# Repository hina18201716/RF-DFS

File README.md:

# Radio Frequency Direction Finding System

The RF-DFS is a controllable 3-meter dish antenna with azimuth and elevation drivers to locate the source of RF interference. Located in this repo is information to connect the motor controllers and a PCB with an upgraded amplifier chain using Mini-Circuits PMA2-63LN+ SMT LNAs.

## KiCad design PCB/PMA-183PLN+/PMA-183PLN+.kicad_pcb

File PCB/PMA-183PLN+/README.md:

# Changelog

## Revision B - 7/5/2023

### Added

- More PTH vias around and directly under RF components.
- Another layer of via picketing around transmission line.
- Silkscreen revision indicator.

### Changed

- Removed Hammond 1554B compatibility due to difficulties in assembly and weatherproofing SMA connectors.

### Fixed

- C9 footprint now correctly matches schematic (0402 --> 1206).
- Moved SMA footprints closer to board edge to reduce filing prior to assembly.

## Revision A - 6/12/2023

### First revision 🎉🎉🎉

- Board is built to 4-layer OSHPark specifications
- Testing shows amplifier oscillates strongly at ~18.5 GHz. This occurs both when the amplifier is biased through the regulator or directly from a DC power supply. SMA landings were also copied from test coupons so that can likely be ruled out. This is possibly due to the lack of PTH vias directly under the IC or the tuning/spacing of picketing around the transmission line.

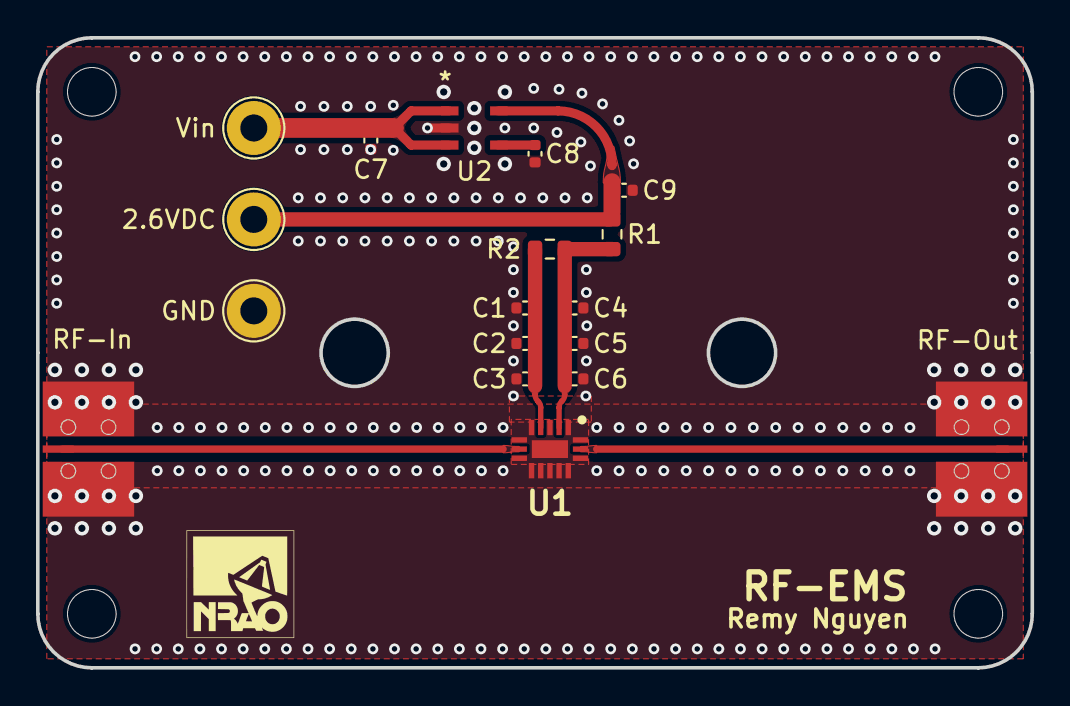
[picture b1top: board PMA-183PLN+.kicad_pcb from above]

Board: 4 copper layers, 55.3 x 35.0 mm, 20 parts (0 on the bottom side), 8 nets.

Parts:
2.6VDC: 2.6VDC; TestPoint_Loop_D2.54mm_Drill1.5mm_Beaded
 : FabDrawing-4Layer-Metric-Compact-OSH
 #2: LOGO; GCPW_osh2_90mm_user
C1, C4, C7: 0.33 uF; C_0402_1005Metric
C2, C5: 1000 pF; C_0402_1005Metric
C3, C6: 100 pF; C_0402_1005Metric
C8: 470 pF; C_0402_1005Metric
C9: 2.2 uF; C_0402_1005Metric
GND: GND; TestPoint_Loop_D2.54mm_Drill1.5mm_Beaded
R1: 10 Ω; R_0603_1608Metric
R2: 180 Ω; R_0603_1608Metric
RF-In: Conn_Coaxial; Mueller BU-1420761881
RF-Out: Conn_Coaxial; Mueller BU-1420761881
U1: PMA-183PLN+; QFN51P250X350X85-17N
U2: MIC5219-2.6YM5-TR; SOT-23-5_M5_MCH
Vin: Vin; TestPoint_Loop_D2.54mm_Drill1.5mm_Beaded

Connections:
2.6VDC: 2.6VDC.1, C9.1, R1.2, U2.5 (OUT)
GND: C1.1, C2.1, C3.1, C4.2, C5.2, C6.2, C7.2, C8.2, C9.2, GND.1, RF-In.2 (Ext), RF-Out.2 (Ext), U1.1 (NC_1), U1.3 (NC_2), U1.5 (NC_3), U1.6 (GND_1), U1.8 (GND_2), U1.9 (NC_4), U1.10 (NC_5), U1.11 (NC_6), U1.12 (NC_7), U1.13 (NC_8), U1.14 (GND_3), U1.16 (GND_4), U1.17 (EP), U2.2 (GND)
unnamed: RF-In.1 (In), U1.7 (RF-IN)
unnamed: RF-Out.1 (In), U1.15 (RF-OUT)
unnamed: C4.1, C5.1, C6.1, R1.1, R2.2, U1.2 (VDD)
unnamed: C1.2, C2.2, C3.2, R2.1, U1.4 (VE)
unnamed: C8.1, U2.4 (BYP)
Vin: C7.1, U2.1 (IN), U2.3 (EN), Vin.1

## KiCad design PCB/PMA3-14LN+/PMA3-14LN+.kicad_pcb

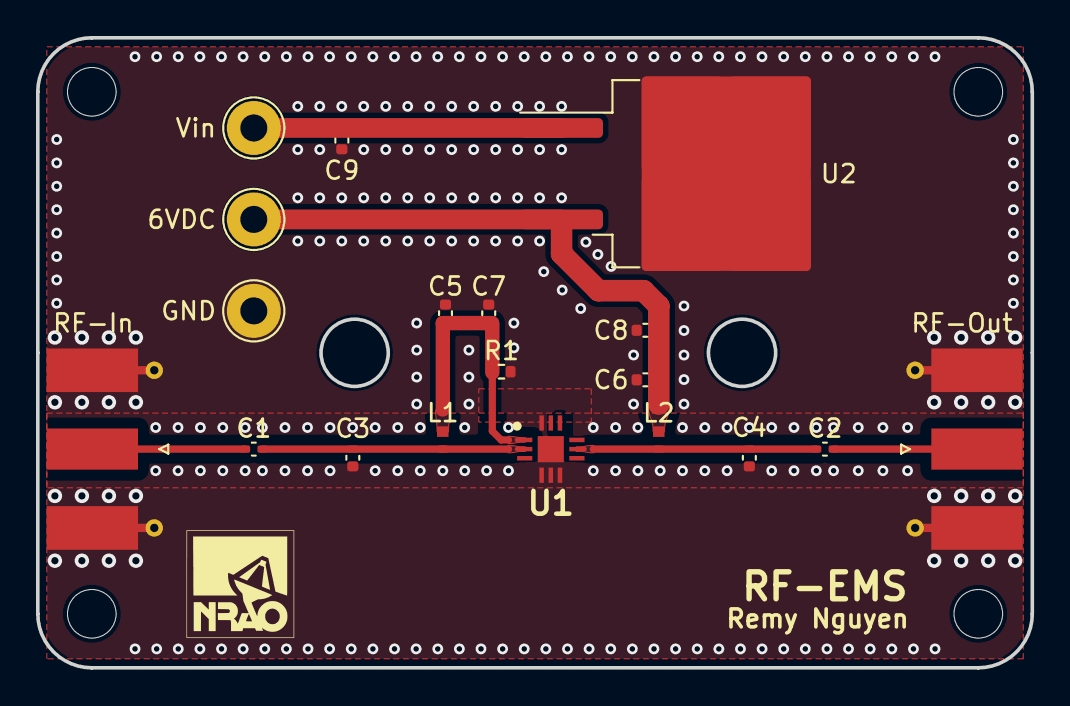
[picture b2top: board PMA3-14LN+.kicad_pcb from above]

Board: 4 copper layers, 55.3 x 35.0 mm, 20 parts (0 on the bottom side), 8 nets.

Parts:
6VDC: 6VDC; TestPoint_Loop_D2.54mm_Drill1.5mm_Beaded
 : FabDrawing-4Layer-Metric-Compact-OSH
C1, C2: 0.01 uF; C_0402_1005Metric
C3: 0.2 pF; C_0402_1005Metric
C4: 0.1 pF; C_0402_1005Metric
C5, C6: 100 pF; C_0402_1005Metric
C7: 0.1 uF; C_0402_1005Metric
C8: 0.1 uf; C_0402_1005Metric
C9: 0.33 uF; C_0402_1005Metric
GND: GND; TestPoint_Loop_D2.54mm_Drill1.5mm_Beaded
L1, L2: 900 nH; L_0402_1005Metric
R1: 510 Ω; R_0402_1005Metric
RF-In: Conn_Coaxial; SMA_Molex_73251-1153_EdgeMount_Horizontal_TunedOSH
RF-Out: Conn_Coaxial; SMA_Molex_73251-1153_EdgeMount_Horizontal_TunedOSH
U1: PMA3-14LN+; QFN51P300X300X89-13N
U2: L7806; TO-263-2
Vin: Vin; TestPoint_Loop_D2.54mm_Drill1.5mm_Beaded

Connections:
6VDC: 6VDC.1, C6.1, C8.1, L2.1, U2.3 (OUT)
GND: C3.1, C4.1, C5.1, C6.2, C7.1, C8.2, C9.2, GND.1, R1.2, RF-In.2 (Ext), RF-Out.2 (Ext), U1.3 (NC_1), U1.4 (NC_2), U1.5 (NC_3), U1.6 (NC_4), U1.7 (NC_5), U1.9 (NC_6), U1.11 (NC_8), U1.12 (NC_9), U1.13 (GND), U2.2 (GND)
unnamed: C5.2, C7.2, L1.1, R1.1, U1.1 (CURRENT_MIRROR)
unnamed: C1.2, C3.2, L1.2, U1.2 (RF-IN)
unnamed: C2.1, C4.2, L2.2, U1.8 (RF-OUT_&_VDD)
unnamed: C1.1, RF-In.1 (In)
unnamed: C2.2, RF-Out.1 (In)
Vin: C9.1, U2.1 (IN), Vin.1

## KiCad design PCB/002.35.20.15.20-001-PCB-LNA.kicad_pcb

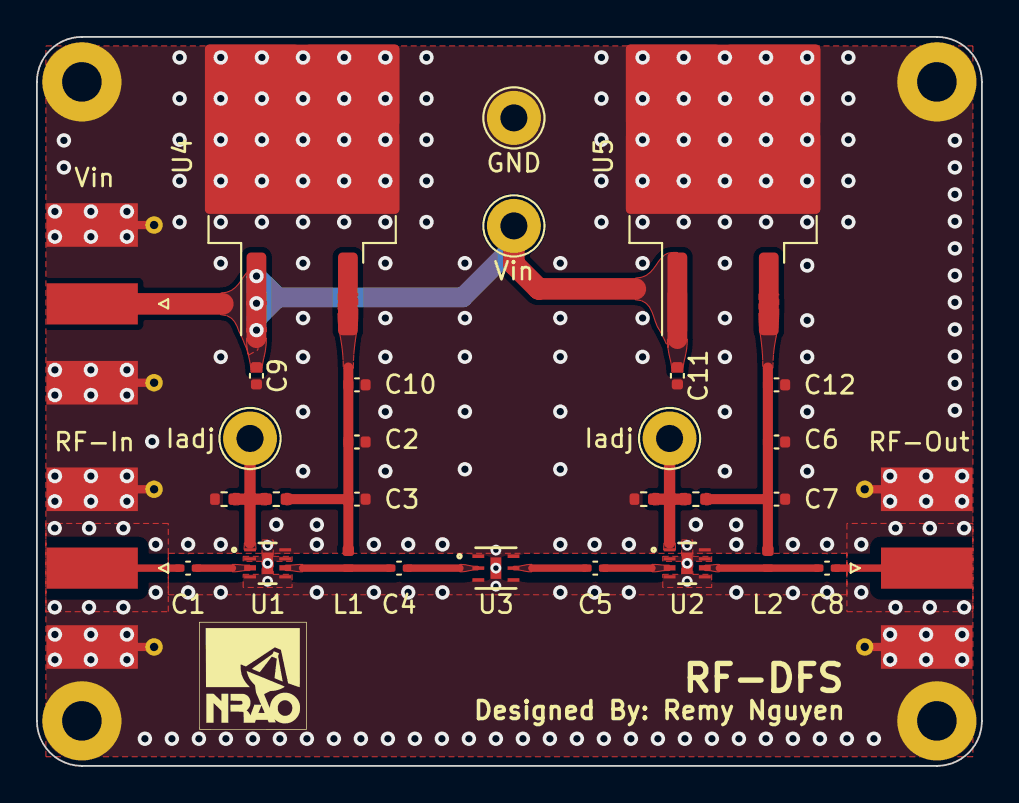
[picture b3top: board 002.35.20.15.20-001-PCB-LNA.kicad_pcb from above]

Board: 4 copper layers, 52.5 x 40.5 mm, 30 parts (0 on the bottom side), 14 nets.

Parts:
C1, C4, C5, C8: 150pF; C_0402_1005Metric
C2, C6: 1uF; C_0402_1005Metric
C3, C7: 100pF; C_0402_1005Metric
C9, C11: 0.33uF; C_0402_1005Metric
C10, C12: 0.1uF; C_0402_1005Metric
GND: GND; TestPoint_Loop_D2.54mm_Drill1.5mm_Beaded
Iadj: TestPoint; TestPoint_Loop_D2.54mm_Drill1.5mm_Beaded
Iadj#2: TestPoint; TestPoint_Loop_D2.54mm_Drill1.5mm_Beaded
L1, L2: 56nH; L_0402_1005Metric
R1, R2, R3, R4: 100k; R_0402_1005Metric
RF-In: Conn_Coaxial; SMA_Molex_73251-1153_EdgeMount_Horizontal
RF-Out: Conn_Coaxial; SMA_Molex_73251-1153_EdgeMount_Horizontal
U1, U2: PMA2-63LN+; SON8_PMA2_MNC
U3: YAT-1A+; MC1630_MNC
U4, U5: L7805; TO-263-2
Vin: Vin; TestPoint_Loop_D2.54mm_Drill1.5mm_Beaded
Vin#2: Conn_Coaxial; SMA_Molex_73251-1153_EdgeMount_Horizontal

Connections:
/LNA Biasing1/LNA-IN: C1.1, RF-In.1 (In)
/LNA Biasing1/LNA-OUT: C4.2, U3.2 (RF-IN)
/LNA Biasing2/LNA-IN: C5.1, U3.5 (RF-OUT)
/LNA Biasing2/LNA-OUT: C8.2, RF-Out.1 (In)
GND: C2.2, C3.2, C6.2, C7.2, C9.2, C10.2, C11.2, C12.2, GND.1, R1.1, R2.1, RF-In.2 (Ext), RF-Out.2 (Ext), U1.2 (GND), U1.4 (GND), U1.5 (GND), U1.7 (GND), U1.8 (GND), U1.9 (EPAD), U2.2 (GND), U2.4 (GND), U2.5 (GND), U2.7 (GND), U2.8 (GND), U2.9 (EPAD), U3.1 (GND), U3.3 (GND), U3.4 (GND), U3.6 (GND), U3.7 (GND), U4.2 (GND), U5.2 (GND), Vin#2.2 (Ext)
unnamed: Iadj#2.1, R1.2, R3.1, U1.1 (LADJ)
unnamed: C1.2, U1.3 (RF-IN)
unnamed: C4.1, L1.2, U1.6 (RF-OUT)
unnamed: Iadj.1, R2.2, R4.1, U2.1 (LADJ)
unnamed: C5.2, U2.3 (RF-IN)
unnamed: C8.1, L2.2, U2.6 (RF-OUT)
Vdd1: C2.1, C3.1, C10.1, L1.1, R3.2, U4.3 (OUT)
Vdd2: C6.1, C7.1, C12.1, L2.1, R4.2, U5.3 (OUT)
Vin: C9.1, C11.1, U4.1 (IN), U5.1 (IN), Vin.1, Vin#2.1 (In)

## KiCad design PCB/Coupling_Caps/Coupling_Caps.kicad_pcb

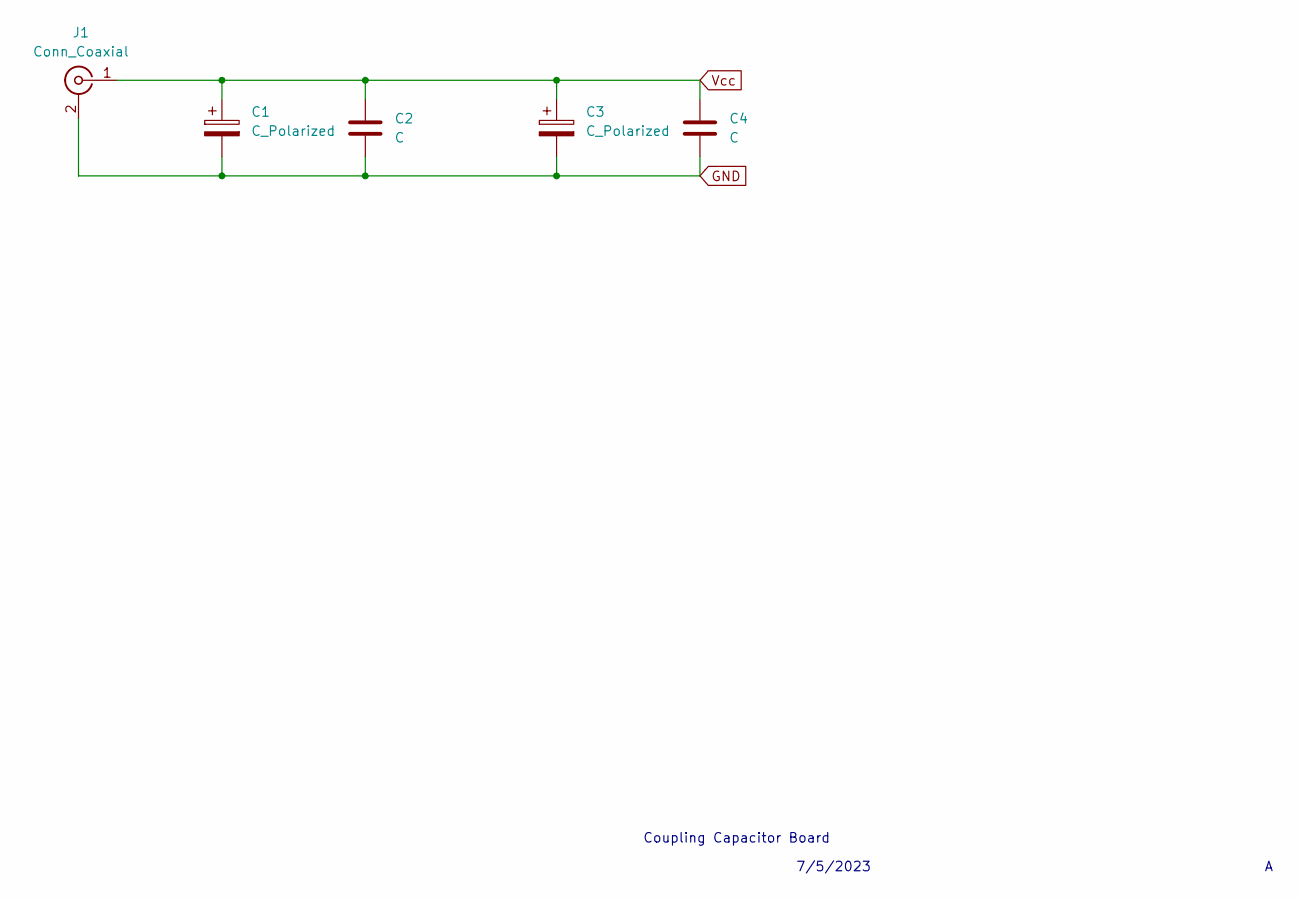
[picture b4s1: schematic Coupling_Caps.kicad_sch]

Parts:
C1, C3: C_Polarized; C_1206_3216Metric
C2, C4: C; C_1206_3216Metric
J1: Conn_Coaxial; SMA_Molex_73251-1153_EdgeMount_Horizontal

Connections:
GND: C1.2, C2.2, C3.2, C4.2, J1.2 (Ext)
Vcc: C1.1, C2.1, C3.1, C4.1, J1.1 (In)

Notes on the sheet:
Coupling Capacitor Board
7/5/2023

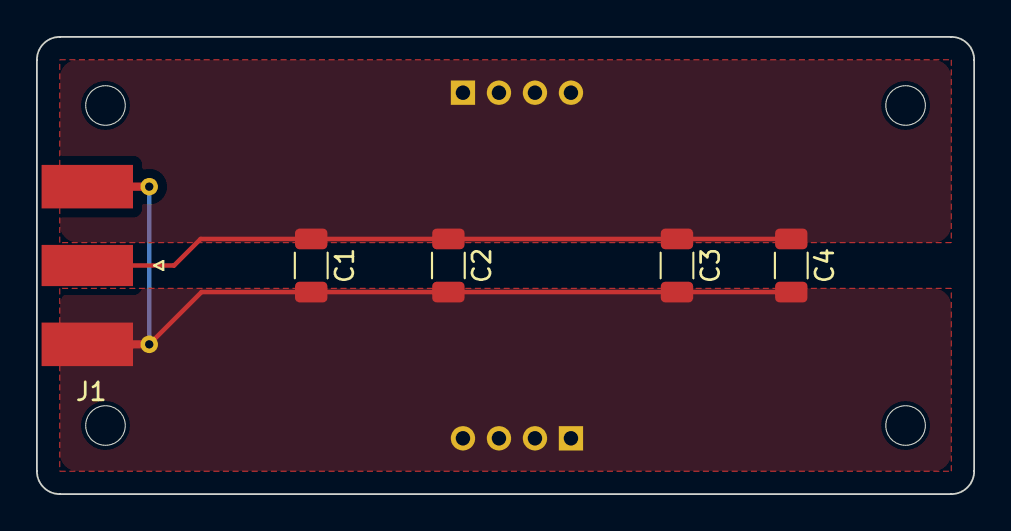
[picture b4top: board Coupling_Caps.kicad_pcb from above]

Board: 2 copper layers, 52.1 x 25.4 mm, 5 parts (0 on the bottom side), 2 nets.

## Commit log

2023-07-06 Initial local commit
2023-07-06 Footprints assigned, ERC pass
2023-07-06 PCB Rev A Complete, DRC Pass
2023-07-07 PTH vias and mounting holes added
2023-07-07 Bill of materials added
2023-07-10 Relocated PTH vias, removed backups
2023-07-10 --no-edit
2023-07-10 10 mil RO4350B --> 30 mil, RF traces adjusted
2023-07-11 Added .gitignore
2023-07-21 Added wiring diagram
2023-07-24 Wiring diagram completed
2023-07-26 Added document numbers
2023-08-02 Added PMA2-63LN+ s-parameters
2023-08-15 6 GHz s-params graphed
2023-08-16 Housekeeping
2023-08-21 Added board comments and assembly plot
2024-01-22 Fixed SMA pad thickness
2024-01-23 PCB Rev B complete: compacted board and fixed sma pads
2024-01-26 Updated board for Oshpark specifications
2024-01-31 New matlab directory with stability simulation
2024-01-31 removed coupling caps board
2024-02-02 Removed back mask from thermal pad and adjusted trace sizes for more accurate z0
2024-02-05 Minor updates to trace width, zone clearance, silkscreen
2024-02-22 PCB Rev C Complete
    * Landing pads improved with testing from Tx-Line boards
    * Mounting holes correctly set to GND net
    * Assembly drawing includes SMA connectors
2024-02-23 Drawing sheets updated
    * A4 --> Letter
    * SMA connector diameter dimensioned
2024-02-27 deleted redundant file
2024-03-07 Updated .gitignore
2024-03-07 New measurements added
    * LNA Rev C scattering parameters added and graphed in MATLAB
    * .s2p files renamed to be more intuitive
2024-03-07 Assembly drawing updated
    * New stackup table format
    * SMA dimensions adjusted to appease mechanicals (it's not technically accurate)
2024-03-08 Added pcb revision changelog
2024-03-08 Added README.md
2024-03-08 Removed files
    - Motor controller manuals
    - LNA evaluation board gerbers
2024-04-11 New LNA design for ENS
    * New PCB directory structure
    * PMA3-14LN+ started with dimensions to fit Hammond Manufacturing 1554B enclosure
    * PMA3-14LN+ chosen for sub-10 GHz
    * PMA-183PLN+ chosen for X band and Ku band
2024-05-03 PMA3-14LN+ design complete sans signal launch tuning
2024-05-03 PMA-183PLN+ design complete sans signal launch tuning
2024-05-03 PMA-183PLN+ schematic pdf added and title text fixed
2024-05-03 Updated silkscreen and reference designators on EMS boards
2024-06-12 PMA-183PLN+ PCB Rev A completed
2024-06-12 TSS-183A+ PCB Rev A completed
2024-06-13 Added tss183 schematic drawing
2024-06-25 initial GUI commit
2024-06-25 Report template added
    - Example figures from solar telescope still present
    - System block diagram drafted
2024-06-26 updated input type checking
2024-06-26 Added emargency stop and park button
2024-06-26 added tempolary port selection functionality
2024-06-27 Updated .gitignore
    - Will not include auxiliary LaTeX files
2024-06-27 System and RF block diagrams drafted
2024-06-28 addeed popup windows for incorrect inputs
2024-06-28 Send comment with Emargency Stop button
2024-07-01 read error message from motro controll test
2024-07-03 avoid error to open port
2024-07-03 improved readability
2024-07-05 Updated .gitignore to remove pcb backups
2024-07-05 Added PMA-183PLN+ changelog
2024-07-05 Fixed: changelog did not commit
2024-07-05 added motor setting window outline
2024-07-08 Updated PMA-183PLN+ changelog
2024-07-08 PMA-183PLN+ Rev B complete
2024-07-08 motor default window
2024-07-08 added free communication window
2024-07-09 error structure change
2024-07-09 error structure changed
2024-07-09 debug type clacification error
2024-07-09 port connection frexibility improved
2024-07-09 serial communication update
2024-07-09 strcturing dymanic label
2024-07-09 improved graphics
2024-07-10 Removed extraneous spreadsheet
2024-07-12 Deleted pycache
2024-07-12 Updated .gitignore to include Python binaries
2024-07-12 Edited user interface for future additions
    - Changed name of `class Newwindow` to `class FrontEnd`
    - FrontEnd now generates tabs for additional utilities
    - New method SerialInterface initializes serial communication on Tab 1
    - Added autoDocString comments
2024-07-12 new test file
2024-07-15 Initial work on frontend VISA control
    - New class VisaControl handles pyVISA commands
    - New method scpiInterface in class FrontEnd on Tab 2
2024-07-15 Program now connects to SCPI device on button press
2024-07-16 New configurations panel in SCPI interface
    - New constants for READ_BYTES and TIMEOUT
    - Panels to set read bytes and timeout
    - Needs: Panels to set Tx/Rx buffer, reading in ASCII/Hex/Binary, and 'Apply' button
    - Needs: Configure panels to actually set VISA parameters
2024-07-17 Repeatability on serial communication improved
2024-07-17 Automatic port selection on each button added
2024-07-17 New method scpiApplyConfig to handle VISA commands from tkinter widgets (Not complete)
2024-07-17 Method connectToRsrc() now tests for for open session before connecting with string passed to it
2024-07-17 New method resetWidgetValues in class FrontEnd to change widget display on tab select event
2024-07-17 Untracked test.py
2024-07-18 Function description added
2024-07-18 scpiApplyConfig now sets VISA attributes on button press
    - readBytes changed to chunkSize due to the way PyVISA handles read buffers
    - New method setConfig in class VisaControl to handle VISA attributes
    - Imported constants from pyvisa package
2024-07-18 Added SCPI instrument refresh button and selection box now resets value on tab select
2024-07-19 update gitignore
2024-07-19 Created close serial communication button
2024-07-19 Added time display
2024-07-19 Added update framework in free serial communication
2024-07-19 Close window button closes window after checking serial port connection is off
2024-07-22 added initialize commands, under testing
2024-07-22 New VISA termination methods frame in GUI
    - Functionality added for sending EOI and termination characters (Does not issue VISA commands yet)
    - Respective variables added to method resetWidgetValues
    - VisaControl object vi instantiated in __init__ of class FrontEnd to allow passing to method resetWidgetValues
    - Fixed documentation in some VisaControl methods
2024-07-23 GUI termination methods frame now issues VISA commands and resets widget values as needed
    - scpiApplyConfig is now called when connecting to a new instrument
    - VisaControl.setConfig receives new arguments and sets EOI/Termination character
2024-07-23 Work only inside of the progrm 0 from ACR
2024-07-30 Data management first commit
2024-07-30 removed setting window
2024-08-01 Embeded Python console
2024-08-01 log data into file with tab delimiter. This is convertable to cvs file
2024-08-01 Improved window visual structure
2024-08-01 datalogging in textfile named time when data starts
2024-08-02 Button to save data and get file was created
2024-08-02 Rearragned Buttons
2024-08-02 Updated DataMagagement so only make one file at one day, and reuse
2024-08-02 Debug error when there is no data savec
2024-08-02 deleted output button
2024-08-06 Added command to close serial when 'X' button is pressed
2024-08-08 Terminal output now scales with window size, added opcodes.py
2024-08-09 Warining Document added
